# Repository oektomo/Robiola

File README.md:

ROBIOLA
==========

# Robot Biola
This Repository will contain PCB and soon a source code for Robot Biola (Violin Robot) hope this will finish and help the one needing this.

This is the feature we want this things will have:

- [ ] adding Battery  
- [ ] adding Battery Charger  
- [ ] adding Battery circuit safer  
- [x] adding USART
- [ ] adding display?
- [x] LED 5V Power indicator
- [ ] Perhaps adding selector for power?
- [x] Switch On-Off indicator
- [ ] SWO debug pin breakout

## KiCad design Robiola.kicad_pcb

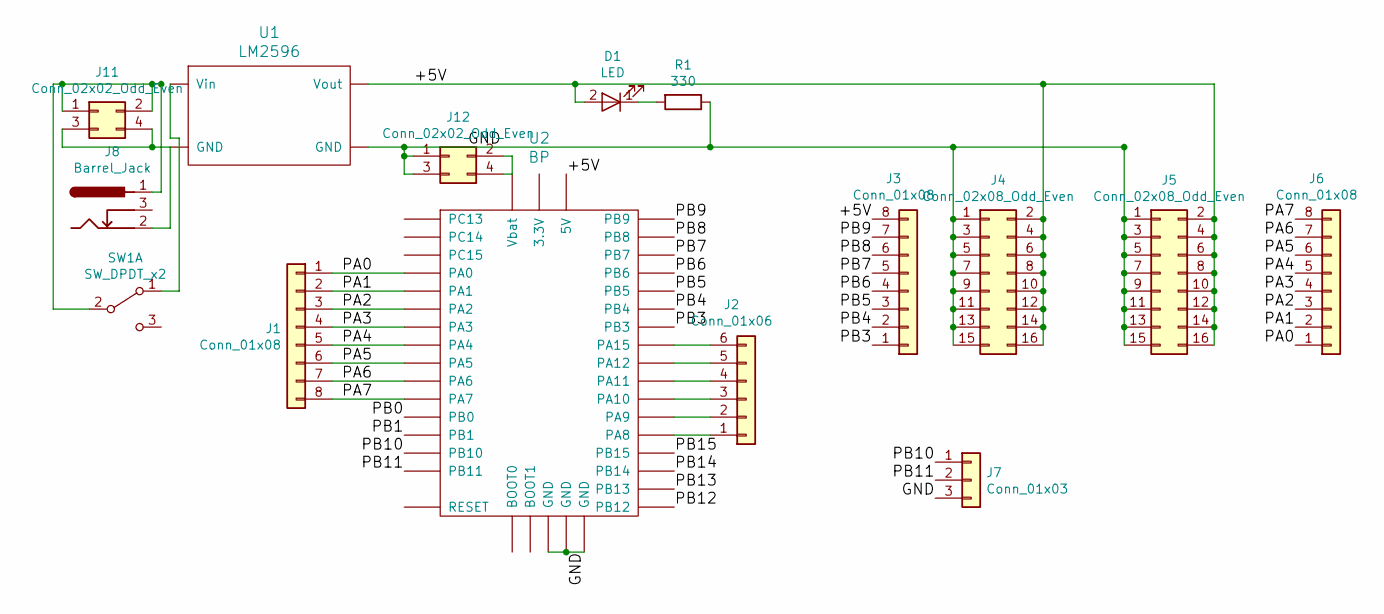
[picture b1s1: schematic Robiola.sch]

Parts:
D1: LED; LED_D3.0mm
J1, J3, J6: Conn_01x08; Pin_Header_Straight_1x08_Pitch2.54mm
J2: Conn_01x06; Pin_Header_Straight_1x06_Pitch2.54mm
J4, J5: Conn_02x08_Odd_Even; Pin_Header_Straight_2x08_Pitch2.54mm
J7: Conn_01x03; Pin_Header_Straight_1x03_Pitch2.54mm
J8: Barrel_Jack; BARREL_JACK
J11, J12: Conn_02x02_Odd_Even; Pin_Header_Straight_2x02_Pitch2.54mm
R1: 330; R_Axial_DIN0204_L3.6mm_D1.6mm_P5.08mm_Horizontal
SW1: SW_DPDT_x2; SW_CuK_JS202011CQN_DPDT_Straight
U1: LM2596; diy-modules-DC-DC-STEP-DOWN-LM2596
U2: BP; DIP-40_W15.24mm_Socket_LongPads

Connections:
/+5V: D1.2 (A), J3.8, J4.2, J4.4, J4.6, J4.8, J4.10, J4.12, J4.14, J4.16, J5.2, J5.4, J5.6, J5.8, J5.10, J5.12, J5.14, J5.16, U1.OUT+ (Vout), U2.18 (5V)
/GND: J4.1, J4.3, J4.5, J4.7, J4.9, J4.11, J4.13, J4.15, J5.1, J5.3, J5.5, J5.7, J5.9, J5.11, J5.13, J5.15, J7.3, J12.1, J12.3, R1.1, U1.OUT- (GND), U2.19 (GND), U2.39 (GND), U2.40 (GND)
/PA0: J1.1, J6.1, U2.25 (PA0)
/PA1: J1.2, J6.2, U2.26 (PA1)
/PA2: J1.3, J6.3, U2.27 (PA2)
/PA3: J1.4, J6.4, U2.28 (PA3)
/PA4: J1.5, J6.5, U2.29 (PA4)
/PA5: J1.6, J6.6, U2.30 (PA5)
/PA6: J1.7, J6.7, U2.31 (PA6)
/PA7: J1.8, J6.8, U2.32 (PA7)
/PB0: U2.33 (PB0)
/PB1: U2.34 (PB1)
/PB3: J3.1, U2.11 (PB3)
/PB4: J3.2, U2.12 (PB4)
/PB5: J3.3, U2.13 (PB5)
/PB6: J3.4, U2.14 (PB6)
/PB7: J3.5, U2.15 (PB7)
/PB8: J3.6, U2.16 (PB8)
/PB9: J3.7, U2.17 (PB9)
/PB10: J7.1, U2.35 (PB10)
/PB11: J7.2, U2.36 (PB11)
/PB12: U2.1 (PB12)
/PB13: U2.2 (PB13)
/PB14: U2.3 (PB14)
/PB15: U2.4 (PB15)
unnamed: D1.1 (K), R1.2
unnamed: J2.1, U2.5 (PA8)
unnamed: J2.2, U2.6 (PA9)
unnamed: J2.3, U2.7 (PA10)
unnamed: J2.4, U2.8 (PA11)
unnamed: J2.5, U2.9 (PA12)
unnamed: J2.6, U2.10 (PA15)
unnamed: J8.1, J11.1, J11.2, SW1.2 (B)
unnamed: J8.2, J11.3, J11.4, U1.IN- (GND)
unnamed: J12.2, J12.4, U2.21 (Vbat)
unnamed: SW1.1 (A), U1.IN+ (Vin)

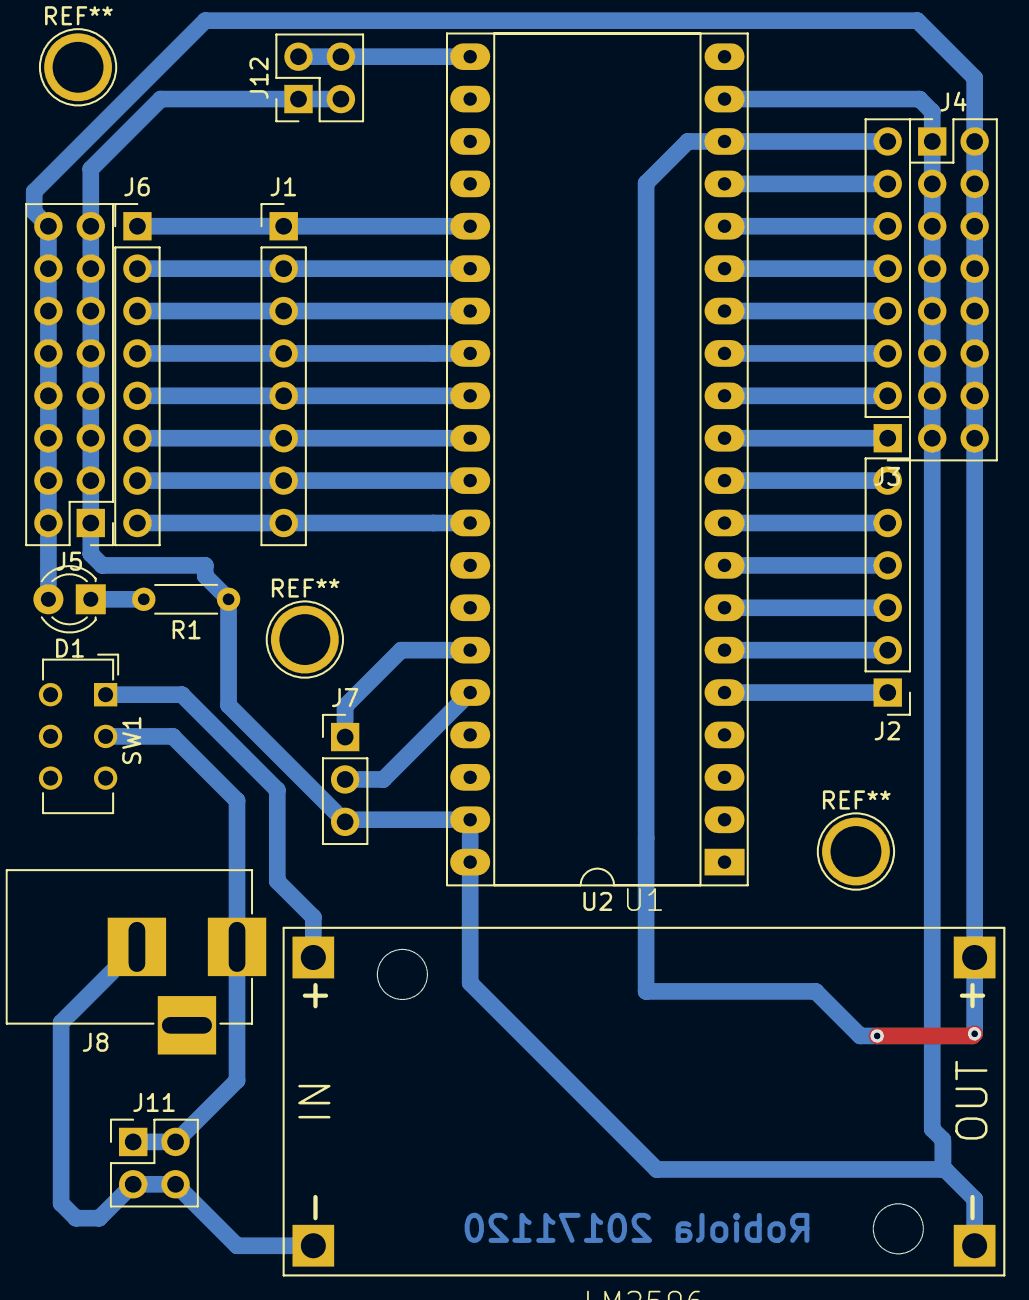
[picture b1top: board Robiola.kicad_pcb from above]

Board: 2 copper layers, 15 parts (0 on the bottom side), 30 nets.

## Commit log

2017-09-27 adding readme
2017-09-27 adding more component
2017-09-27 README.md little mod
2017-09-28 add desc in readme, adding some connection
2017-09-28 fixing a header, adding size estimation, add wanted feature to README
2017-11-19 finishing ver 1
2017-11-19 updating README.md with feature and checklist
2017-11-19 correcting README.md
2017-11-19 adding *.pdf and correcting missinformation in README.md
